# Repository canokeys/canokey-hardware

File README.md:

# CanoKey Hardware Design

This repository contains schematics, PCB projects, and Gerber files of Canokeys.

## Hardware Variants

- `CanoKey NFC-A`: The Canokey with on-board USB Type-A connector and NFC antenna.
- `CanoKey NFC-C`: The Canokey with USB Type-C connector and NFC antenna.
- `CanoKey Nano-A`: The small-sized Canokey which fits inside USB Type-A port.

## License

All hardware, unless otherwise noted, is dual-licensed under CERN and CC-BY-SA. You may use CanoKey hardware under the terms of either the CERN 1.2 license or CC-BY-SA 4.0 license.

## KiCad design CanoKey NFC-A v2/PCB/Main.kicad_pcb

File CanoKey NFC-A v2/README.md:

# CanoKey NFC-A v2

This repository contains circuitry, circuit board designs, and Gerber files for Canokeys.

This catalog contains a modified version of the CanoKey NFC-A board

Benefits:

- The project was created in a full-fledged CAD system KiCad
- All components are available in LCSC
- The project is prepared for automatic assembly on JLCPCB
- Well-designed circuit diagram
- Hardware compatible with CanoKey NFC-A
- Redesigned PCB design and topology

Differences in hardware:

- Redesigned ESD protection
- Added 3x floral LED
- Changed device configuration concept (HW-Rev-CFG), will allow a greater variety of options
- More sensitive NFC antenna
- USB differential pair matched

Component library and small instructions can be found in the public repository

https://github.com/MuratovAS/KiCadLibrary

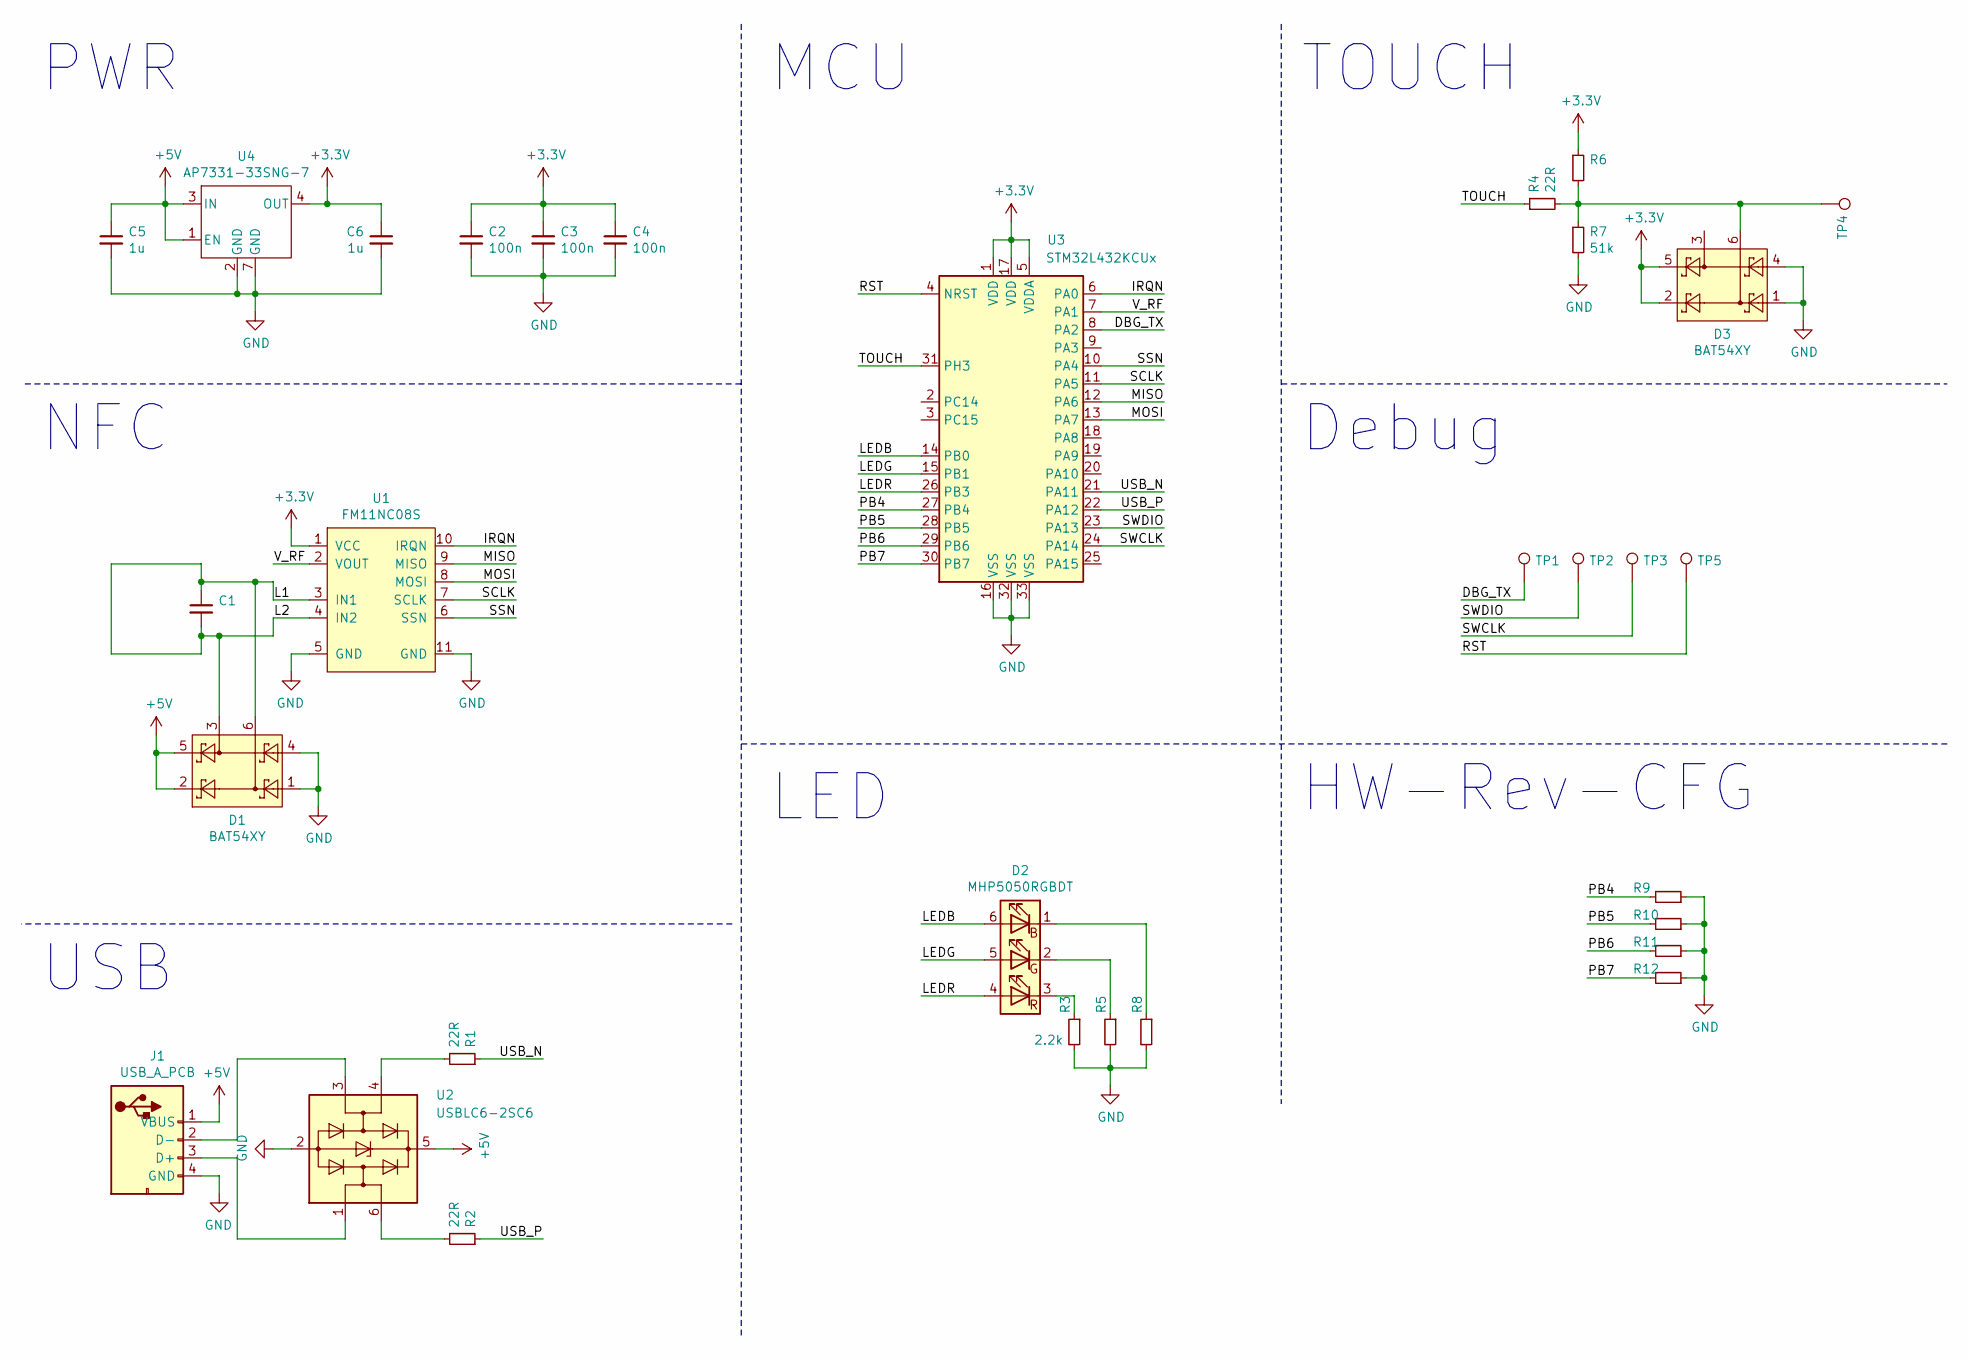
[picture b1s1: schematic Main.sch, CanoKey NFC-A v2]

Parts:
C1: C_0603_1608Metric; Voltage 50v
C2, C3, C4: 100n; C_0603_1608Metric; Voltage 50v; LCSC C14663
C5, C6: 1u; C_0603_1608Metric; Voltage 25v; LCSC C15849
D1, D3: BAT54XY; SOT-363_SC-70-6; LCSC C282367
D2: MHP5050RGBDT; LED_RGB_5050-6; LCSC C409780
J1: USB_A_PCB
R1, R2, R4: 22R; R_0603_1608Metric; Tolerance 5%; LCSC C23345
R3, R5, R8: 2.2k; R_0603_1608Metric; Tolerance 5%; LCSC C4190
R6, R9, R10, R11, R12: R_0603_1608Metric; Tolerance 5%
R7: 51k; R_0603_1608Metric; Tolerance 5%; LCSC C23196
TP1, TP2, TP3, TP5: TestPoint; TestPoint_Pad_D1.0mm
TP4: TestPoint; TestPoint_Pad_D4.0mm
U1: FM11NC08S; DFN-10-1EP_3x3mm_P0.5mm_EP1.55x2.48mm; LCSC C182885
U2: USBLC6-2SC6; SOT-23-6; LCSC C7519
U3: STM32L432KCUx; QFN-32-1EP_5x5mm_P0.5mm_EP3.45x3.45mm; LCSC C94784
U4: AP7331-33SNG-7; UDFN-6-1EP_2x2mm_P0.65mm_EP0.9x1.65mm; LCSC C150446

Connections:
+3V3: C2.1, C3.1, C4.1, C6.1, D3.2, D3.5, R6.1, U1.1 (VCC), U3.1 (VDD), U3.5 (VDDA), U3.17 (VDD), U4.4 (OUT)
+5V: C5.1, D1.2, D1.5, J1.1 (VBUS), U2.5 (VBUS), U4.1 (EN), U4.3 (IN)
/DBG_TX: TP1.1, U3.8 (PA2)
/IRQN: U1.10 (IRQN), U3.6 (PA0)
/L1: C1.1, C1.2, D1.3, D1.6, U1.3 (IN1), U1.4 (IN2)
/LEDB: D2.6 (BK), U3.14 (PB0)
/LEDG: D2.5 (RK), U3.15 (PB1)
/LEDR: D2.4 (GK), U3.26 (PB3)
/MISO: U1.9 (MISO), U3.12 (PA6)
/MOSI: U1.8 (MOSI), U3.13 (PA7)
/PB4: R9.2, U3.27 (PB4)
/PB5: R10.2, U3.28 (PB5)
/PB6: R11.2, U3.29 (PB6)
/PB7: R12.2, U3.30 (PB7)
/RST: TP5.1, U3.4 (NRST)
/SCLK: U1.7 (SCLK), U3.11 (PA5)
/SSN: U1.6 (SSN), U3.10 (PA4)
/SWCLK: TP3.1, U3.24 (PA14)
/SWDIO: TP2.1, U3.23 (PA13)
/TOUCH: R4.1, U3.31 (PH3)
/USB_N: R1.1, U3.21 (PA11)
/USB_P: R2.1, U3.22 (PA12)
/V_RF: U1.2 (VOUT), U3.7 (PA1)
GND: C2.2, C3.2, C4.2, C5.2, C6.2, D1.1, D1.4, D3.1, D3.4, J1.4 (GND), R3.2, R5.2, R7.2, R8.2, R9.1, R10.1, R11.1, R12.1, U1.5 (GND), U1.11 (GND), U2.2 (GND), U3.16 (VSS), U3.32 (VSS), U3.33 (VSS), U4.2 (GND), U4.7 (GND)
unnamed: D2.1 (BA), R8.1
unnamed: D2.2 (RA), R5.1
unnamed: D2.3 (GA), R3.1
unnamed: D3.6, R4.2, R6.2, R7.1, TP4.1
unnamed: J1.2 (D-), U2.3 (I/O2)
unnamed: J1.3 (D+), U2.1 (I/O1)
unnamed: R1.2, U2.4 (I/O2)
unnamed: R2.2, U2.6 (I/O1)

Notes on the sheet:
HW-Rev-CFG
Debug
TOUCH
LED
USB
NFC
PWR
MCU

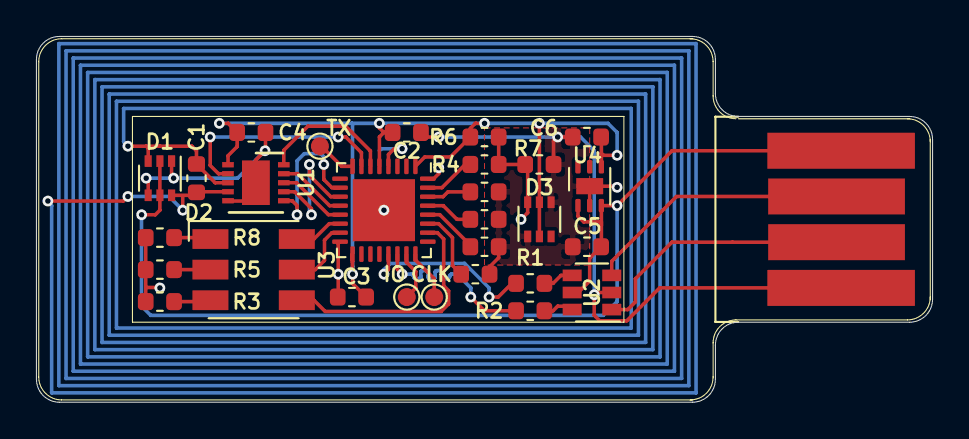
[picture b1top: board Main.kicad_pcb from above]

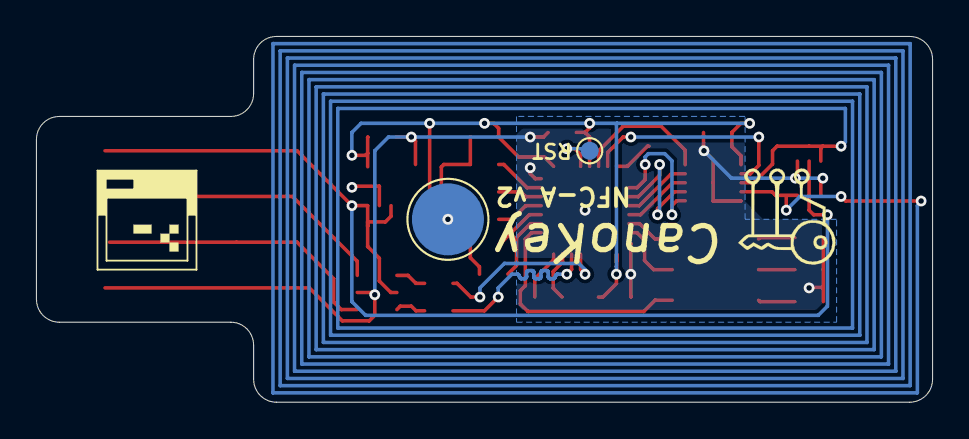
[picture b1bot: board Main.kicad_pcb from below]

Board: 2 copper layers, 49.8 x 20.3 mm, 31 parts (2 on the bottom side), 32 nets.

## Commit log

2020-06-10 add hardware design files
2020-06-11 fix comment text
2020-06-20 update comments
2020-06-20 add Nano-A
2020-06-26 CanoKey Nano-A: Sync PCB capacitor value from schematic
2020-07-01 add NFC-C
2020-07-01 add pcb
2020-07-01 add Manufacturing File
2020-07-01 add readme
2022-03-25 update PCB project
